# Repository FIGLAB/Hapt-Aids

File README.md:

# Hapt-Aids: Self-Powered, On-Body Haptics for Activity Monitoring
This is the repository for Hapt-Aids, presented at UBICOMP 2025. Check out the [full paper here](https://drive.google.com/file/d/1-sPkwGhYdYCn-X2jhVIx13SwtfONY48X/view?usp=sharing)!
Feel free to contact me with any questions!

The JLCPCB folder can be directly uploaded, and should also contain instructions for assembly of the PCB with all components other than the supercapacitor and the vibration motor.

If you want to edit the files, open the project in KICAD.
The full parts list can be found in the Bill of Materials.

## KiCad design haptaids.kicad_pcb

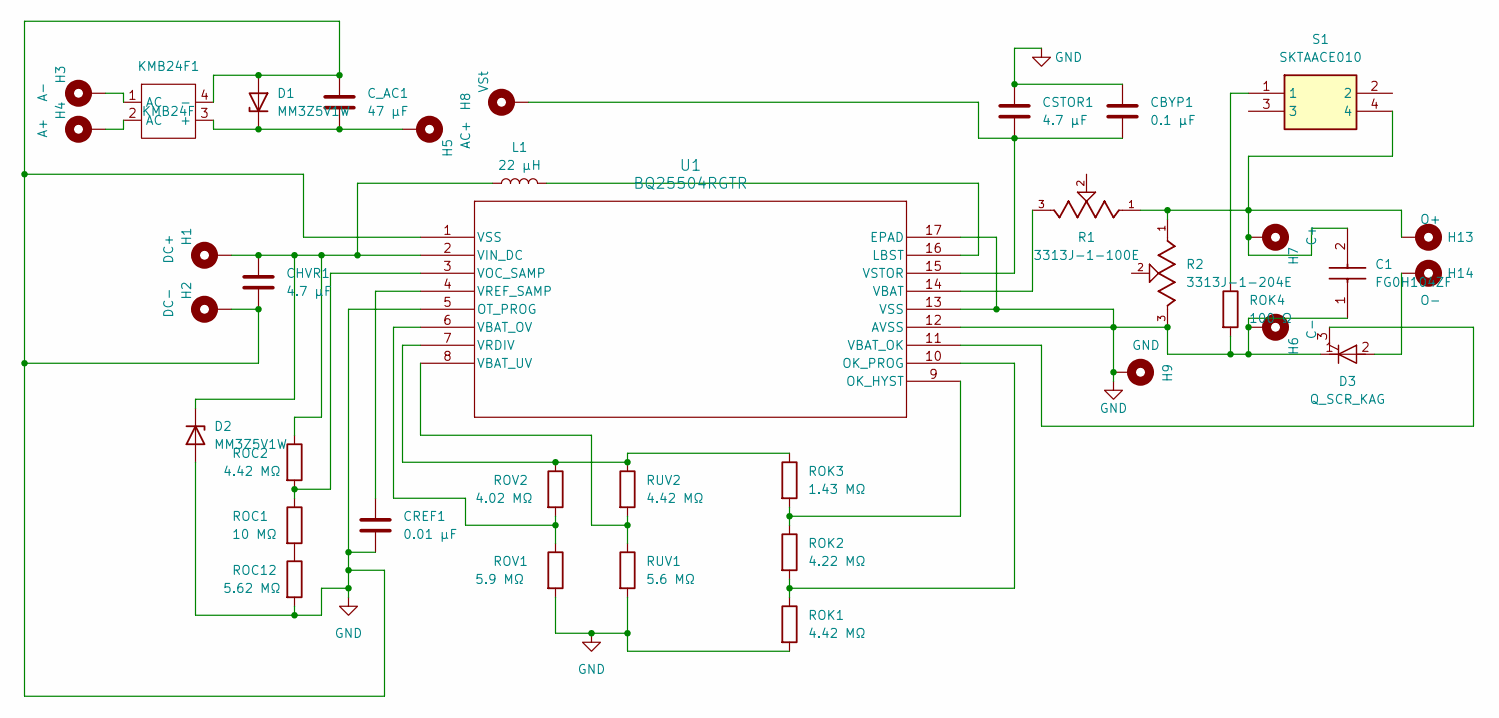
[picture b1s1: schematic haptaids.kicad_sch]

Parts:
C1: FG0H104ZF; CAPPRD508W114D1100H650; Mouser Part Number 80-FG0H104ZF
CBYP1: 0.1 μF; C_0402_1005Metric
CHVR1: 4.7 μF; C_0402_1005Metric
CREF1: 0.01 μF; C_0402_1005Metric
CSTOR1: 4.7 μF; C_0402_1005Metric
C_AC1: 47 μF; C_0603_1608Metric
D1, D2: MM3Z5V1W; D_SOD-323
D3: Q_SCR_KAG; SCR_small
H1: DC+; PinHeader_1x01_P1.00mm_Vertical
H2: DC-; PinHeader_1x01_P1.00mm_Vertical
H3: A-; PinHeader_1x01_P1.00mm_Vertical
H4: A+; PinHeader_1x01_P1.00mm_Vertical
H5: AC+; PinHeader_1x01_P1.00mm_Vertical
H6: C-; PinHeader_1x01_P1.00mm_Vertical
H7: C+; PinHeader_1x01_P1.00mm_Vertical
H9: GND; PinHeader_1x01_P1.00mm_Vertical
H13: O+; PinHeader_1x01_P1.00mm_Vertical
H14: O-; PinHeader_1x01_P1.00mm_Vertical
KMB24F1: KMB24F; DIO-BG-SMD_MBF-TL
L1: 22 μH; L_Changjiang_FNR4026S
R1: 3313J-1-100E; TRIM_3313J-1-100E; PARTREV 08/19
R2: 3313J-1-204E; TRIM_3313J-1-100E; PARTREV 08/19
ROC1: 10 MΩ; R_0402_1005Metric
ROC2: 4.42 MΩ; R_0402_1005Metric
ROC12: 5.62 MΩ; R_0402_1005Metric
ROK1: 4.42 MΩ; R_0402_1005Metric
ROK2: 4.22 MΩ; R_0402_1005Metric
ROK3: 1.43 MΩ; R_0402_1005Metric
ROK4: 100 Ω; R_0402_1005Metric
ROV1: 5.9 MΩ; R_0402_1005Metric
ROV2: 4.02 MΩ; R_0402_1005Metric
RUV1: 5.6 MΩ; R_0402_1005Metric
RUV2: 4.42 MΩ; R_0402_1005Metric
S1: SKTAACE010; Mouser Part Number 688-SKTAACE010
U1: BQ25504RGTR; RGT16_1P7X1P7
VSt: H8; PinHeader_1x01_P1.00mm_Vertical

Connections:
GND: C1.1 (+), CBYP1.2, CHVR1.1, CREF1.1, CSTOR1.2, C_AC1.2, D1.2 (A), D2.2 (A), D3.1 (K), H2.1, H6.1, H9.1, KMB24F1.4 (-), R2.3, ROC12.2, ROK1.2, ROK4.2, ROV1.2, RUV1.2, U1.1 (VSS), U1.5 (OT_PROG), U1.12 (AVSS), U1.13 (VSS), U1.17 (EPAD)
unnamed: C1.2 (-), H7.1, H13.1, R1.1, R2.1, S1.4
unnamed: C_AC1.1, D1.1 (K), H5.1, KMB24F1.3 (+)
unnamed: CHVR1.2, D2.1 (K), H1.1, L1.1, ROC2.1, U1.2 (VIN_DC)
unnamed: D3.2 (A), H14.1
unnamed: D3.3 (G), U1.11 (VBAT_OK)
unnamed: H3.1, KMB24F1.1 (AC)
unnamed: H4.1, KMB24F1.2 (AC)
unnamed: ROC1.2, ROC12.1
unnamed: ROK4.1, S1.1
unnamed: L1.2, U1.16 (LBST)
unnamed: ROK2.1, ROK3.2, U1.9 (OK_HYST)
unnamed: ROK1.1, ROK2.2, U1.10 (OK_PROG)
unnamed: R1.3, U1.14 (VBAT)
unnamed: ROV1.1, ROV2.2, U1.6 (VBAT_OV)
unnamed: RUV1.1, RUV2.2, U1.8 (VBAT_UV)
unnamed: ROC1.1, ROC2.2, U1.3 (VOC_SAMP)
unnamed: ROK3.1, ROV2.1, RUV2.1, U1.7 (VRDIV)
unnamed: CREF1.2, U1.4 (VREF_SAMP)
unnamed: CBYP1.1, CSTOR1.1, U1.15 (VSTOR), VSt.1

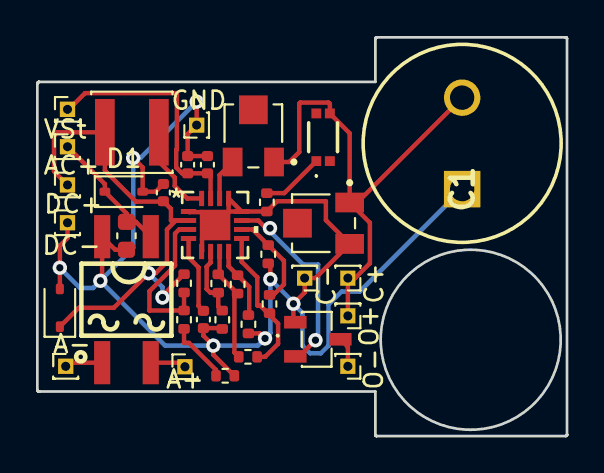
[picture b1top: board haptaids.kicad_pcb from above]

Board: 2 copper layers, 29.4 x 22.2 mm, 37 parts (0 on the bottom side), 20 nets.

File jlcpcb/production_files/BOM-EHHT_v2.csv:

Comment,Designator,Footprint,LCSC
MCR16,D3,MCR16,
A+,H4,PinHeader_1x01_P1.00mm_Vertical,
0.01uF,CREF1,Capacitor_SMD:C_0402_1005Metric,
O+,H13,PinHeader_1x01_P1.00mm_Vertical,
4.42M,RUV2,Resistor_SMD:R_0402_1005Metric,
0.1uF,CBYP1,Capacitor_SMD:C_0402_1005Metric,
4.7uF,CHVR1,Capacitor_SMD:C_0402_1005Metric,
10M,ROC1,Resistor_SMD:R_0402_1005Metric,
5.62M,ROC12,Resistor_SMD:R_0402_1005Metric,
4.22M,ROK2,Resistor_SMD:R_0402_1005Metric,
DC+,H1,PinHeader_1x01_P1.00mm_Vertical,
BQ25504RGTT,U1,RGT16_1P7X1P7,
4.7uF,CSTOR1,Capacitor_SMD:C_0402_1005Metric,
SKTAACE010,S1,SKTAACE010,
3313J-1-100E,R1,TRIM_3313J-1-100E,
DC-,H2,PinHeader_1x01_P1.00mm_Vertical,
4.42M,ROK1,Resistor_SMD:R_0402_1005Metric,
100,ROK4,Resistor_SMD:R_0402_1005Metric,
MM3Z5V1W,D1,D_SOD-323,
47uF,C_AC1,Capacitor_SMD:C_0603_1608Metric,
4.02M,ROV2,Resistor_SMD:R_0402_1005Metric,
KMB24F,KMB24F1,DIO-BG-SMD_MBF-TL,
C+,H7,PinHeader_1x01_P1.00mm_Vertical,
4.42M,ROC2,Resistor_SMD:R_0402_1005Metric,
AC+,H5,PinHeader_1x01_P1.00mm_Vertical,
C-,H6,PinHeader_1x01_P1.00mm_Vertical,
3313J-1-204E,R2,TRIM_3313J-1-100E,
22uH,L1,CMLW4030S220MST,
5.6M,RUV1,Resistor_SMD:R_0402_1005Metric,
GND,H9,PinHeader_1x01_P1.00mm_Vertical,
MM3Z5V1W,D2,D_SOD-323,
5.9M,ROV1,Resistor_SMD:R_0402_1005Metric,
O-,H14,PinHeader_1x01_P1.00mm_Vertical,
1.43M,ROK3,Resistor_SMD:R_0402_1005Metric,
A-,H3,PinHeader_1x01_P1.00mm_Vertical,

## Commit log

2025-12-19 PCB Files
